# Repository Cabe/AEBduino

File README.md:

# AEBduino
AEBuino is an open hardware project for controlling Nerf (and other) blasters.

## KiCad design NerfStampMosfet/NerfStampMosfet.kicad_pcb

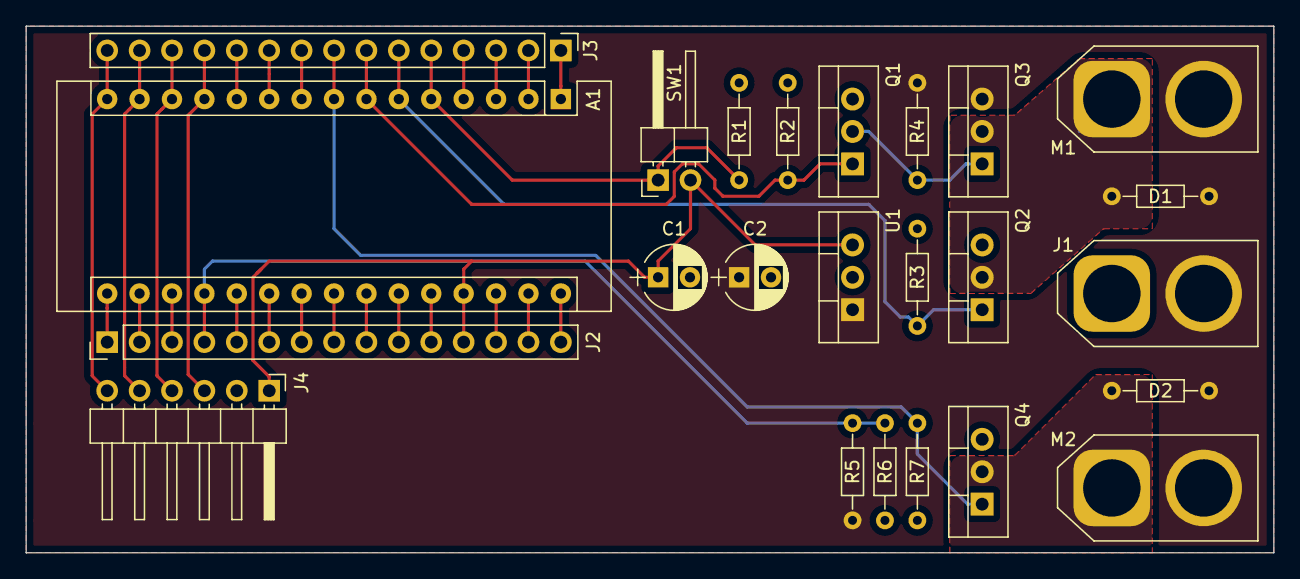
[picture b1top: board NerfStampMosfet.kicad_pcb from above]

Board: 2 copper layers, 97.8 x 41.3 mm, 24 parts (0 on the bottom side), 34 nets.

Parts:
A1: Arduino_Nano_v3.x; Arduino_Nano
C1, C2: 10uF; CP_Radial_D5.0mm_P2.50mm
D1, D2: DIODE; R_Axial_DIN0204_L3.6mm_D1.6mm_P7.62mm_Horizontal
J1: Conn_01x02_Male; AMASS_XT60-M_1x02_P7.20mm_Vertical
J2, J3: Conn_01x15_Male; Pin_Header_Straight_1x15_Pitch2.54mm
J4: Conn_01x06_Male; Pin_Header_Angled_1x06_Pitch2.54mm
M1, M2: Motor_DC_Flipped; AMASS_XT60-F_1x02_P7.20mm_Vertical
Q1, Q2, Q4: IRF540N; TO-220-3_Vertical
Q3: IRF4905; TO-220-3_Vertical
R1, R4: 10K; R_Axial_DIN0204_L3.6mm_D1.6mm_P7.62mm_Horizontal
R2, R3, R7: 1K; R_Axial_DIN0204_L3.6mm_D1.6mm_P7.62mm_Horizontal
R5: 1M; R_Axial_DIN0204_L3.6mm_D1.6mm_P7.62mm_Horizontal
R6: 100k; R_Axial_DIN0204_L3.6mm_D1.6mm_P7.62mm_Horizontal
SW1: SW_Push; Pin_Header_Angled_1x02_Pitch2.54mm
U1: LM7805_TO220; TO-220-3_Vertical

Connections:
+5V: A1.27, C1.1, J2.12, J4.1, SW1.2, U1.3
+BATT: C2.1, D1.2, D2.2, J1.2, M1.2, M2.2, Q3.3, R4.2, R5.1, U1.1
GND: A1.4, C1.2, C2.2, J1.1, J3.4, J4.2, Q1.3, Q2.3, Q4.3, R1.1, R2.2, R3.2, R6.2, R7.2, U1.2
unnamed: A1.1, J3.1
unnamed: A1.2, J3.2
unnamed: A1.3, J3.3
unnamed: A1.5, J3.5, R1.2, SW1.1
unnamed: A1.6, J3.6, Q2.1, R3.1
unnamed: A1.7, J3.7, Q1.1, R2.1
unnamed: A1.8, J3.8, Q4.1, R7.1
unnamed: A1.9, J3.9
unnamed: A1.10, J3.10
unnamed: A1.11, J3.11
unnamed: A1.12, J3.12, J4.3
unnamed: A1.13, J3.13, J4.4
unnamed: A1.14, J3.14, J4.5
unnamed: A1.15, J3.15, J4.6
unnamed: A1.16, J2.1
unnamed: A1.17, J2.2
unnamed: A1.18, J2.3
unnamed: A1.19, J2.4, R5.2, R6.1
unnamed: A1.20, J2.5
unnamed: A1.21, J2.6
unnamed: A1.22, J2.7
unnamed: A1.23, J2.8
unnamed: A1.24, J2.9
unnamed: A1.25, J2.10
unnamed: A1.26, J2.11
unnamed: A1.28, J2.13
unnamed: A1.29, J2.14
unnamed: A1.30, J2.15
unnamed: D1.1, M1.1, Q2.2, Q3.2
unnamed: D2.1, M2.1, Q4.2
unnamed: Q1.2, Q3.1, R4.1

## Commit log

2019-12-21 Initial Commit of PCB design - UNTESTED
    Not gonna lie, as a unit this untested and should be treated like the fire risk it might be :)
